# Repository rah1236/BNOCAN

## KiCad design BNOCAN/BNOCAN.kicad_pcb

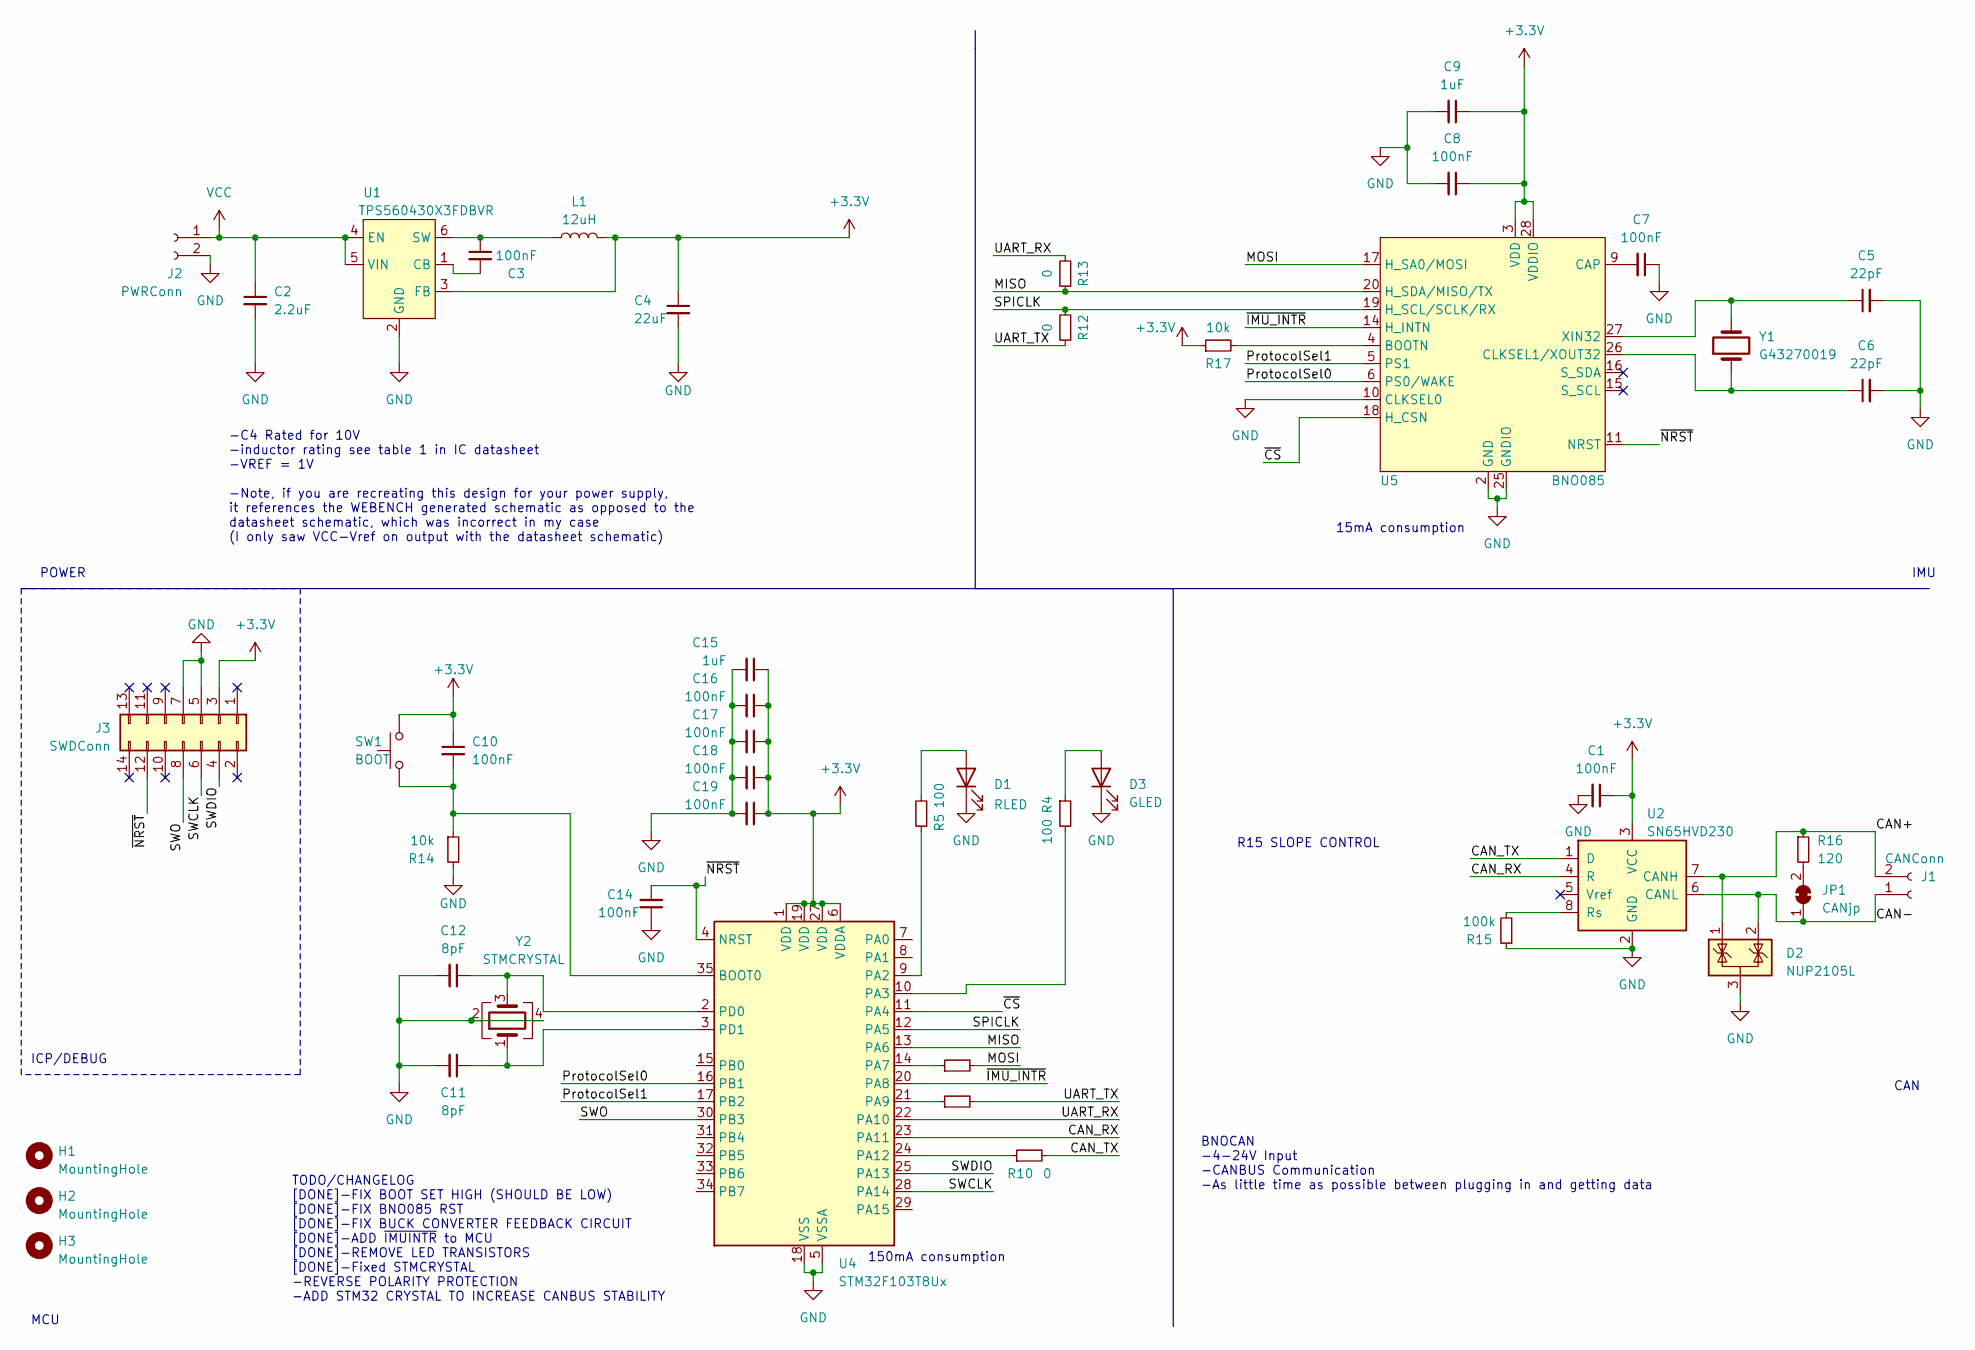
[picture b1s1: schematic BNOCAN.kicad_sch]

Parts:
C1, C3, C7, C8, C10, C14, C16, C17, C18, C19: 100nF; C_0402_1005Metric
C2: 2.2uF; C_0603_1608Metric
C4: 22uF; C_0402_1005Metric
C5, C6: 22pF; C_0402_1005Metric
C9, C15: 1uF; C_0603_1608Metric
C11, C12: 8pF; C_0402_1005Metric
D1: RLED; LED_0603_1608Metric
D2: NUP2105L; SOT-23
D3: GLED; LED_0603_1608Metric
H1, H2, H3: MountingHole; MountingHole_3.2mm_M3
J1: CANConn; SolderWire-0.15sqmm_1x02_P4mm_D0.5mm_OD1.5mm_Relief
J2: PWRConn; SolderWire-0.15sqmm_1x02_P4mm_D0.5mm_OD1.5mm_Relief
J3: SWDConn; PinHeader_2x07_P1.27mm_Vertical_SMD
JP1: CANjp; PinHeader_1x02_P2.54mm_Vertical
L1: 12uH; L_1210_3225Metric
R4, R5: 100; R_0402_1005Metric
R9, R10, R11, R12, R13: 0; R_0402_1005Metric
R14, R17: 10k; R_0603_1608Metric
R15: 100k; R_0603_1608Metric
R16: 120; R_0805_2012Metric_Pad1.20x1.40mm_HandSolder
SW1: BOOT; SW_SPST_TL3305A
U1: TPS560430X3FDBVR; SOT-23-6
U2: SN65HVD230; SOIC-8_3.9x4.9mm_P1.27mm
U4: STM32F103T8Ux; QFN-36-1EP_6x6mm_P0.5mm_EP4.1x4.1mm
U5: BNO085; LGA-28_5.2x3.8mm_P0.5mm
Y1: G43270019; Crystal_SMD_3215-2Pin_3.2x1.5mm
Y2: STMCRYSTAL; Crystal_SMD_3225-4Pin_3.2x2.5mm

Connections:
+3.3V: C1.1, C4.1, C8.1, C9.1, C10.1, C15.1, C16.1, C17.1, C18.1, C19.1, J3.3, L1.2, R17.1, SW1.2, U1.3 (FB), U2.3 (VCC), U4.1 (VDD), U4.6 (VDDA), U4.19 (VDD), U4.27 (VDD), U5.3 (VDD), U5.28 (VDDIO)
/CAN+: D2.1 (K), J1.2, R16.1, U2.7 (CANH)
/CAN-: D2.2 (K), J1.1, JP1.1 (A), U2.6 (CANL)
/CAN_RX: U2.4 (R), U4.23 (PA11)
/CAN_TX: R10.2, U2.1 (D)
/MISO: R13.1, U4.13 (PA6), U5.20 (H_SDA/MISO/TX)
/MOSI: R11.2, U5.17 (H_SA0/MOSI)
/ProtocolSel0: U4.16 (PB1), U5.6 (PS0/WAKE)
/ProtocolSel1: U4.17 (PB2), U5.5 (PS1)
/SPICLK: R12.2, U4.12 (PA5), U5.19 (H_SCL/SCLK/RX)
/SWCLK: J3.6, U4.28 (PA14)
/SWDIO: J3.4, U4.25 (PA13)
/SWO: J3.8, U4.30 (PB3)
/UART_RX: R13.2, U4.22 (PA10)
/UART_TX: R9.2, R12.1
/~CS: U4.11 (PA4), U5.18 (H_CSN)
/~IMU_INTR: U4.20 (PA8), U5.14 (H_INTN)
/~NRST: C14.2, J3.12, U4.4 (NRST), U5.11 (NRST)
GND: C1.2, C2.2, C4.2, C5.2, C6.2, C7.1, C8.2, C9.2, C11.2, C12.2, C14.1, C15.2, C16.2, C17.2, C18.2, C19.2, D1.1 (K), D2.3 (A), D3.1 (K), J2.2, J3.5, J3.7, R14.2, R15.1, U1.2 (GND), U2.2 (GND), U4.5 (VSSA), U4.18 (VSS), U4.26 (VSS), U4.36 (VSS), U4.37 (VSS), U5.2 (GND), U5.10 (CLKSEL0), U5.25 (GNDIO), Y2.2, Y2.4
unnamed: D1.2 (A), R5.2
unnamed: D3.2 (A), R4.1
unnamed: JP1.2 (B), R16.2
unnamed: C3.2, U1.1 (CB)
unnamed: C3.1, L1.1, U1.6 (SW)
unnamed: R15.2, U2.8 (Rs)
unnamed: C10.2, R14.1, SW1.1, U4.35 (BOOT0)
unnamed: R5.1, U4.9 (PA2)
unnamed: R4.2, U4.10 (PA3)
unnamed: R11.1, U4.14 (PA7)
unnamed: R9.1, U4.21 (PA9)
unnamed: R10.1, U4.24 (PA12)
unnamed: C12.1, U4.2 (PD0), Y2.3
unnamed: C11.1, U4.3 (PD1), Y2.1
unnamed: R17.2, U5.4 (BOOTN)
unnamed: C7.2, U5.9 (CAP)
unnamed: C6.1, U5.26 (CLKSEL1/XOUT32), Y1.1
unnamed: C5.1, U5.27 (XIN32), Y1.2
VCC: C2.1, J2.1, U1.4 (EN), U1.5 (VIN)

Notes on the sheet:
R15 SLOPE CONTROL
ICP/DEBUG
BNOCAN -4-24V Input -CANBUS Communication -As little time as possible between plugging in and getting data
15mA consumption
MCU
IMU
-C4 Rated for 10V -inductor rating see table 1 in IC datasheet -VREF = 1V -Note, if you are recreating this design for your power supply, it references the WEBENCH generated schematic as opposed to the datasheet schematic, which was incorrect in my case (I only saw VCC-Vref on output with the datas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
CAN
TODO/CHANGELOG [DONE]-FIX BOOT SET HIGH (SHOULD BE LOW) [DONE]-FIX BNO085 RST [DONE]-FIX BUCK CONVERTER FEEDBACK CIRCUIT [DONE]-ADD ~{IMUINTR} to MCU [DONE]-REMOVE LED TRANSISTORS [DONE]-Fixed STMCRYSTAL -REVERSE POLARITY PROTECTION -ADD STM32 CRYSTAL TO INCREASE CANBUS STABILITY
POWER
150mA consumption

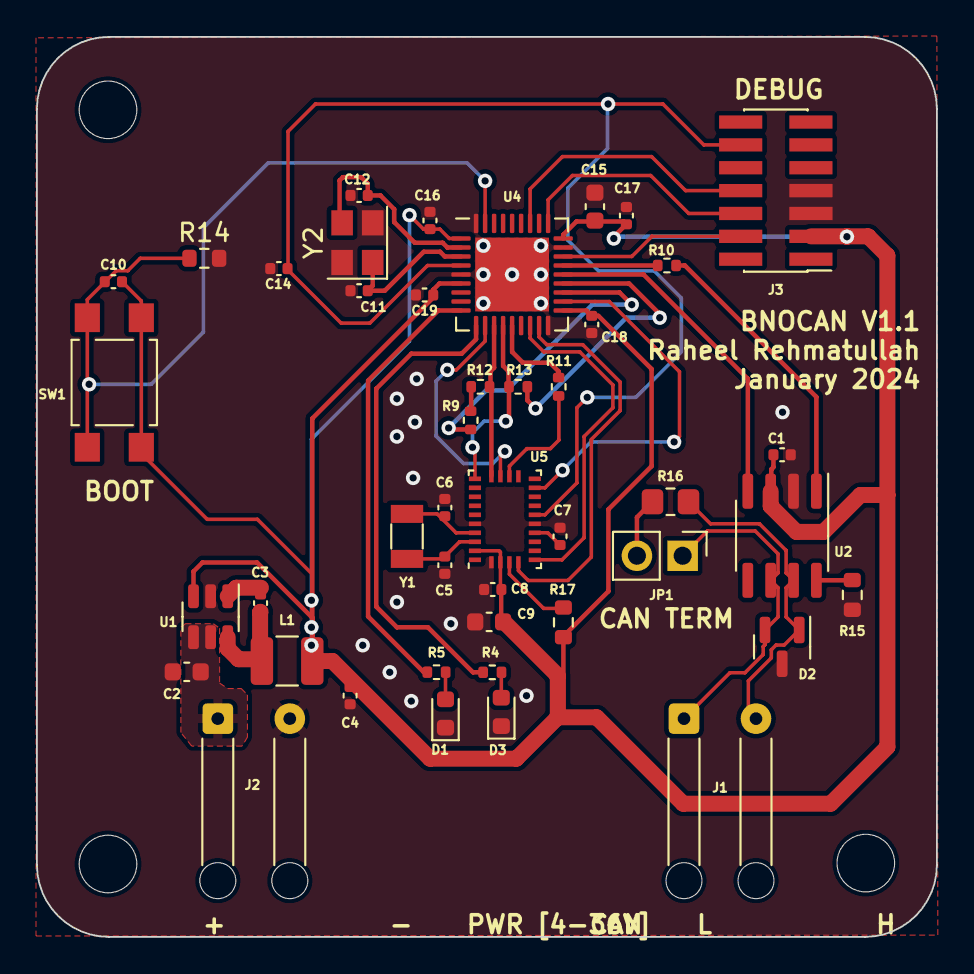
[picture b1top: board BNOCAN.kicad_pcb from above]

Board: 2 copper layers, 50.0 x 50.0 mm, 47 parts (0 on the bottom side), 38 nets.

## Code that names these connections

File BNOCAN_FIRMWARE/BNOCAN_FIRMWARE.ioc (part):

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Mcu.Name=STM32F103T(8-B)Ux
Mcu.Package=VFQFPN36
Mcu.UserName=STM32F103T8Ux
PA10.Mode=Asynchronous
PA10.Signal=USART1_RX
PA11.Mode=CAN_Activate
PA11.Signal=CAN_RX
PA12.Mode=CAN_Activate
PA12.Signal=CAN_TX
PA13.Mode=Serial_Wire
PA13.Signal=SYS_JTMS-SWDIO
PA14.Mode=Serial_Wire
PA14.Signal=SYS_JTCK-SWCLK
PA2.Signal=S_TIM2_CH3
PA3.GPIOParameters=GPIO_Label
PA3.GPIO_Label=RED_LED
PA3.Signal=S_TIM2_CH4
PA8.GPIOParameters=GPIO_Label,GPIO_ModeDefaultEXTI
PA8.GPIO_Label=IMU_INTR
PA8.GPIO_ModeDefaultEXTI=GPIO_MODE_IT_FALLING
PA8.Signal=GPXTI8
PA9.Mode=Asynchronous
PA9.Signal=USART1_TX
PB1.GPIOParameters=GPIO_PuPd,GPIO_Label
PB1.GPIO_Label=PS0/WAKE
PB1.GPIO_PuPd=GPIO_PULLUP
PB1.Signal=GPIO_Output
PB2.GPIOParameters=GPIO_PuPd,GPIO_Label
PB2.GPIO_Label=PS1
PB2.GPIO_PuPd=GPIO_PULLUP
PB2.Signal=GPIO_Output
PB3.Signal=SYS_JTDO-TRACESWO
PD0-OSC_IN.Mode=HSE-External-Oscillator
PD0-OSC_IN.Signal=RCC_OSC_IN
PD1-OSC_OUT.Mode=HSE-External-Oscillator
PD1-OSC_OUT.Signal=RCC_OSC_OUT
RCC.SYSCLKFreq_VALUE=72000000
RCC.SYSCLKSource=RCC_SYSCLKSOURCE_PLLCLK
board=custom

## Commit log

2023-12-19 V1 Ordered
2024-03-23 V1.1 Produced
2024-04-07 Firmware Dump + some Board Bug fixes
